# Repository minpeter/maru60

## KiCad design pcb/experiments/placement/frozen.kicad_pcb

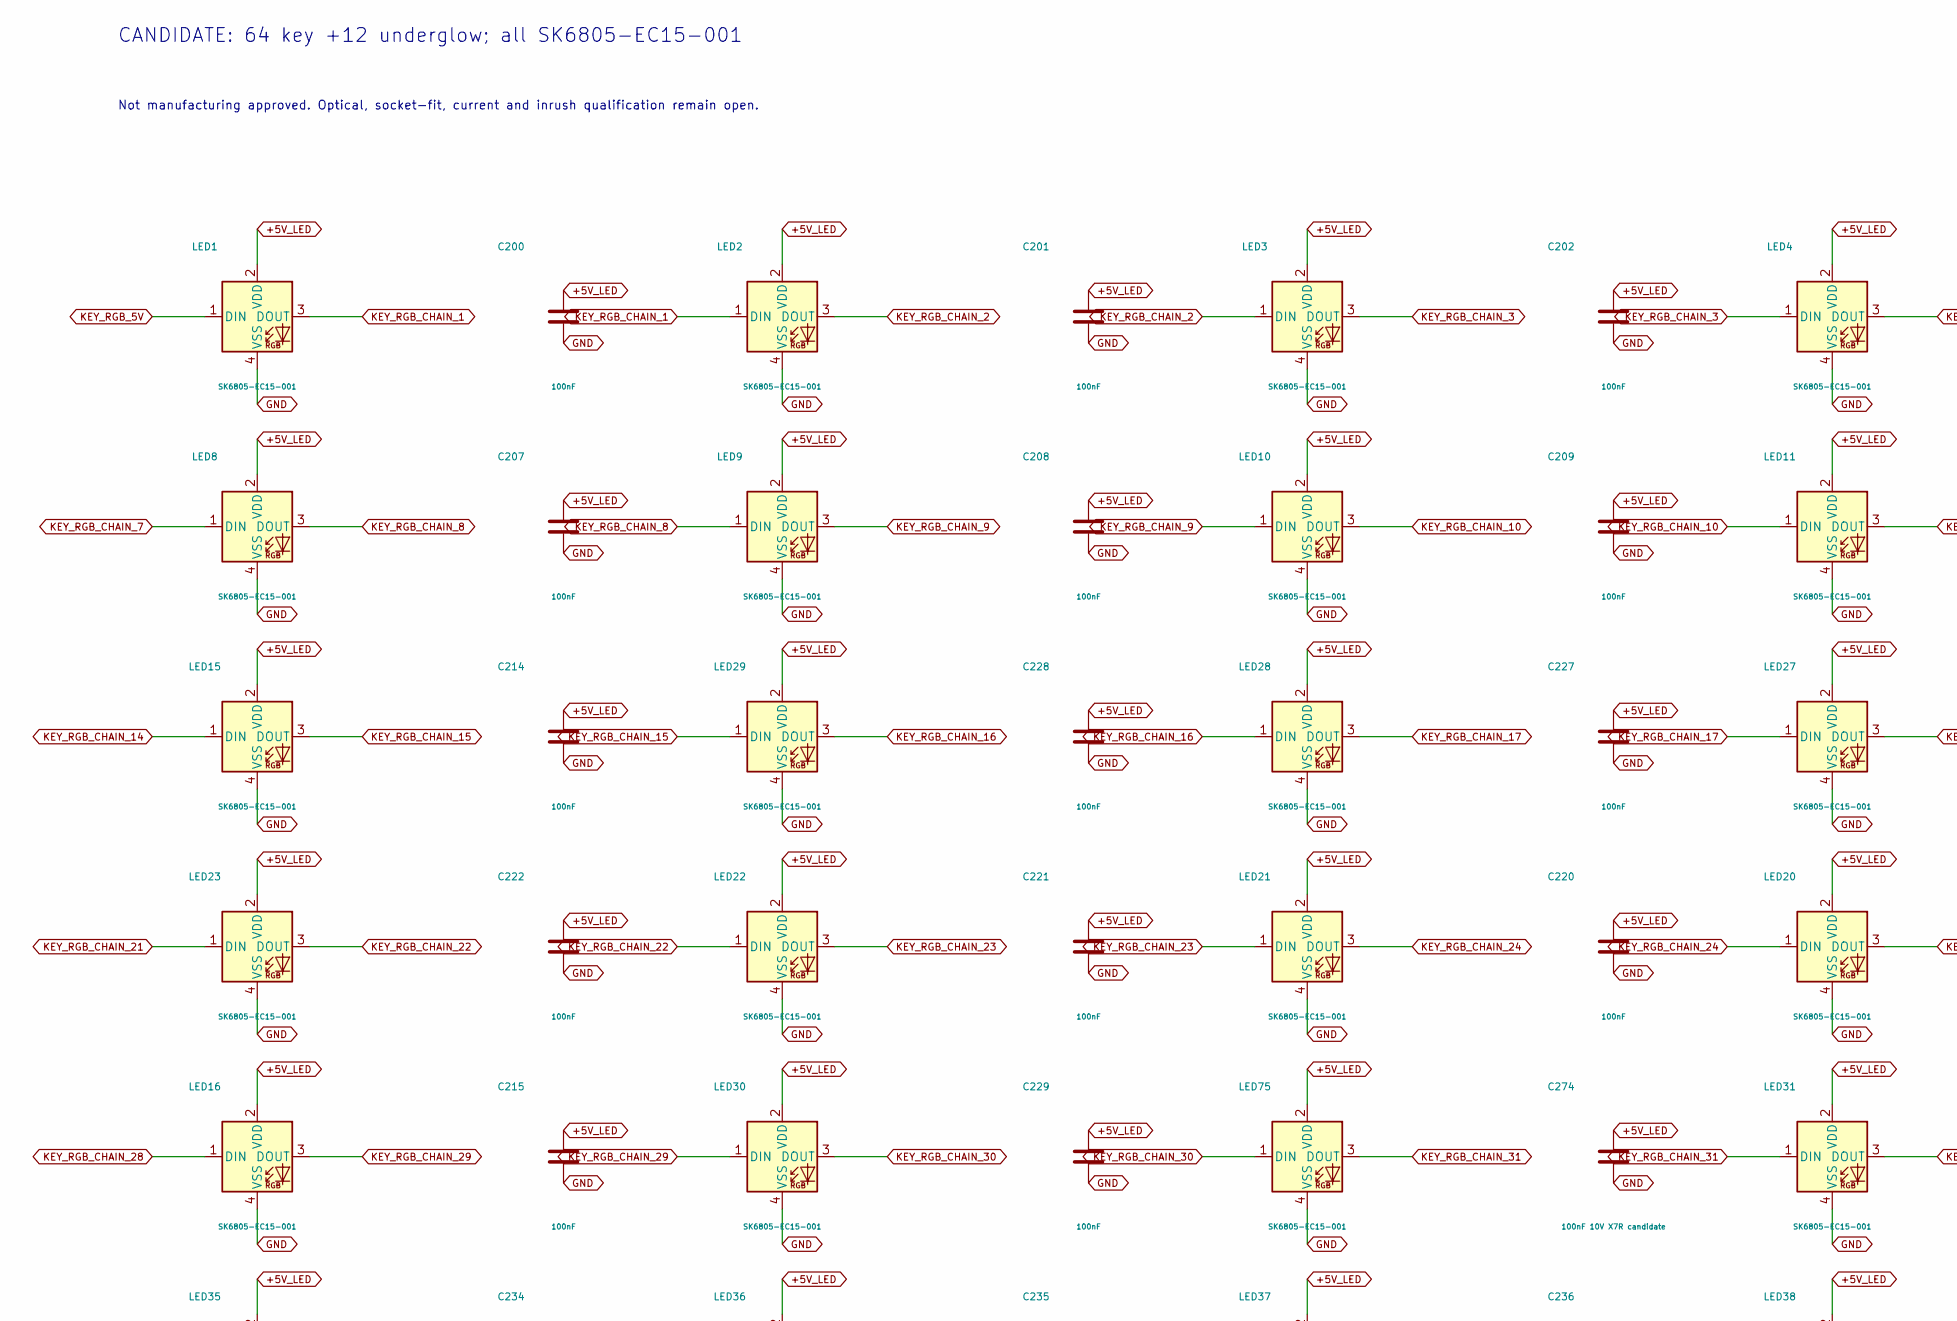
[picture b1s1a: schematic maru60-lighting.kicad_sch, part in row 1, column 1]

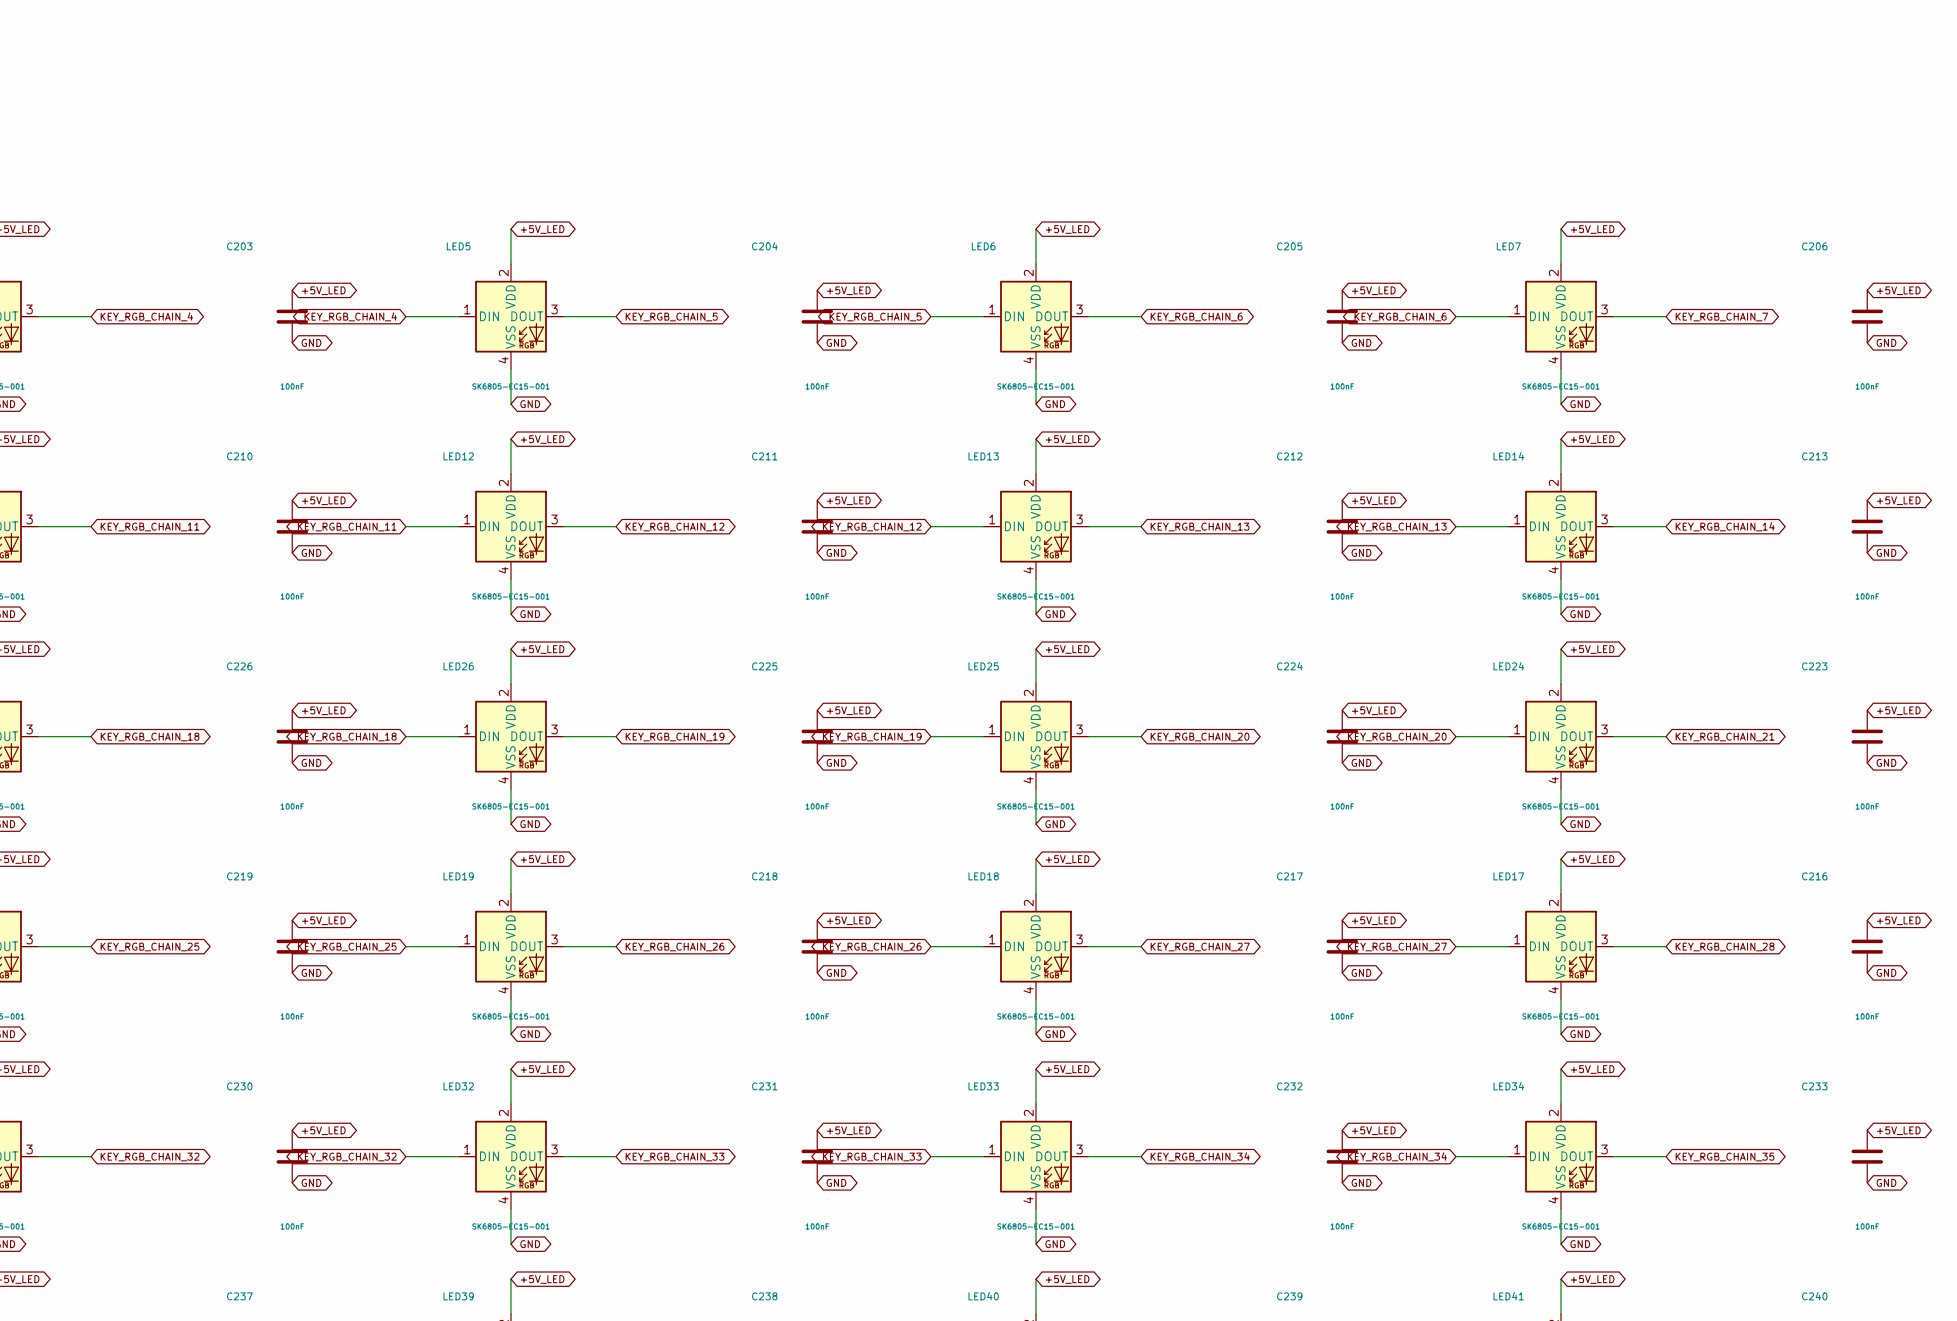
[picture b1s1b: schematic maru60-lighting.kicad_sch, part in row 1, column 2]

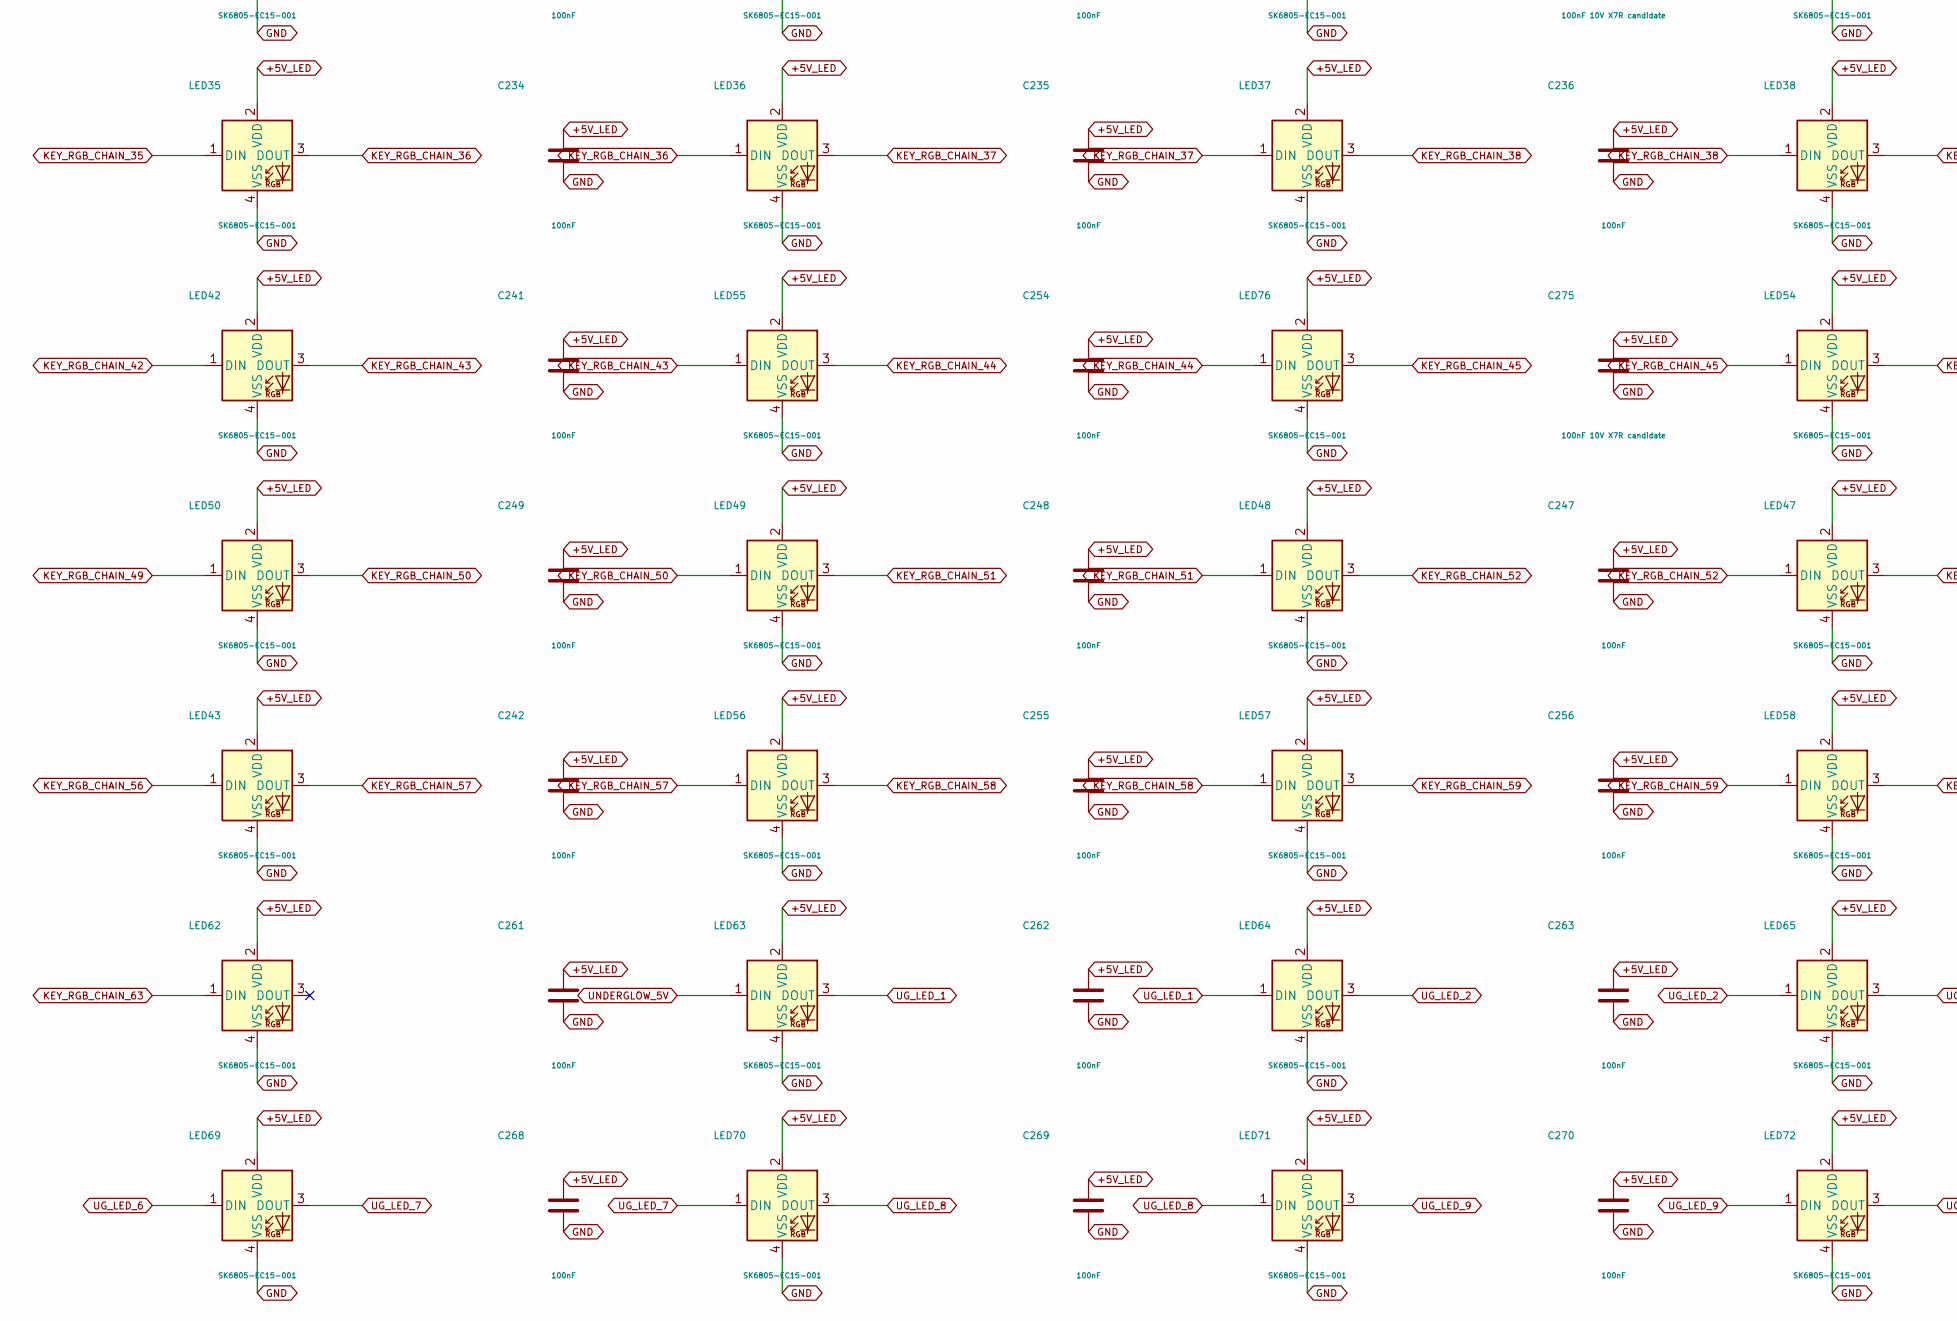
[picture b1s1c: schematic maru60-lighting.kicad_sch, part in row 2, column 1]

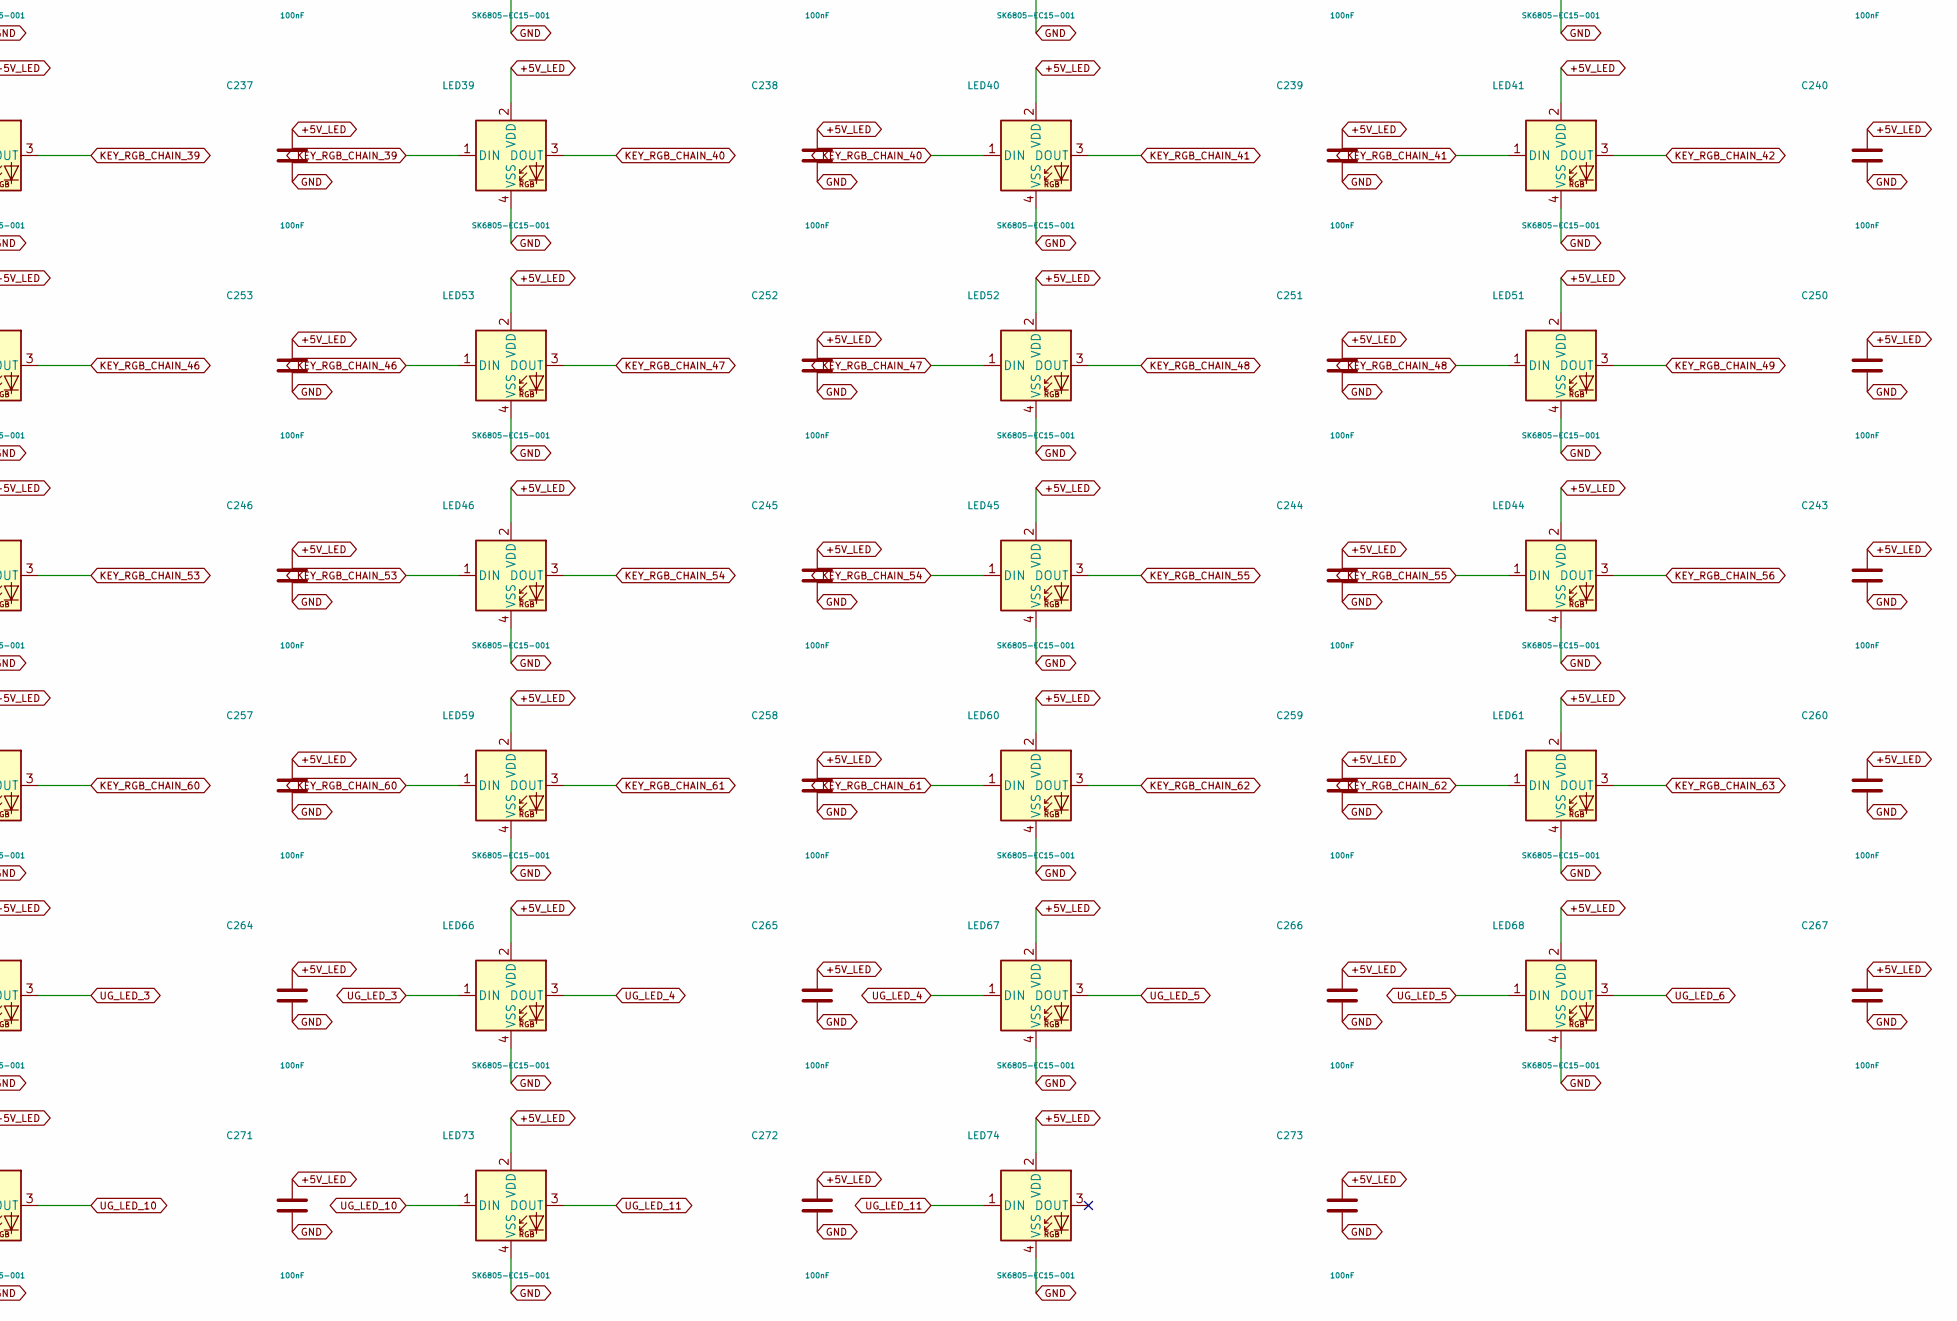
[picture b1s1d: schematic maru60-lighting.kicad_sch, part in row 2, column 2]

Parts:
C200, C201, C202, C203, C204, C205, C206, C207, C208, C209, C210, C211, C212, C213, C214, C215, C216, C217, C218, C219, C220, C221, C222, C223, C224, C225, C226, C227, C228, C229, C230, C231, C232, C233, C234, C235, C236, C237, C238, C239, C240, C241, C242, C243, C244, C245, C246, C247, C248, C249, C250, C251, C252, C253, C254, C255, C256, C257, C258, C259, C260, C261, C262, C263, C264, C265, C266, C267, C268, C269, C270, C271, C272, C273: 100nF; C_0402_1005Metric
C274, C275: 100nF 10V X7R candidate; C_0402_1005Metric
LED1, LED2, LED3, LED4, LED5, LED6, LED7, LED8, LED9, LED10, LED11, LED12, LED13, LED14, LED15, LED16, LED17, LED18, LED19, LED20, LED21, LED22, LED23, LED24, LED25, LED26, LED27, LED28, LED29, LED30, LED31, LED32, LED33, LED34, LED35, LED36, LED37, LED38, LED39, LED40, LED41, LED42, LED43, LED44, LED45, LED46, LED47, LED48, LED49, LED50, LED51, LED52, LED53, LED54, LED55, LED56, LED57, LED58, LED59, LED60, LED61, LED62, LED63, LED64, LED65, LED66, LED67, LED68, LED69, LED70, LED71, LED72, LED73, LED74, LED75, LED76: SK6805-EC15-001; LED_SK6805_EC15_001_Recommended_Candidate

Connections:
+5V_LED: C200.1, C201.1, C202.1, C203.1, C204.1, C205.1, C206.1, C207.1, C208.1, C209.1, C210.1, C211.1, C212.1, C213.1, C214.1, C215.1, C216.1, C217.1, C218.1, C219.1, C220.1, C221.1, C222.1, C223.1, C224.1, C225.1, C226.1, C227.1, C228.1, C229.1, C230.1, C231.1, C232.1, C233.1, C234.1, C235.1, C236.1, C237.1, C238.1, C239.1, C240.1, C241.1, C242.1, C243.1, C244.1, C245.1, C246.1, C247.1, C248.1, C249.1, C250.1, C251.1, C252.1, C253.1, C254.1, C255.1, C256.1, C257.1, C258.1, C259.1, C260.1, C261.1, C262.1, C263.1, C264.1, C265.1, C266.1, C267.1, C268.1, C269.1, C270.1, C271.1, C272.1, C273.1, C274.1, C275.1, LED1.2 (VDD), LED2.2 (VDD), LED3.2 (VDD), LED4.2 (VDD), LED5.2 (VDD), LED6.2 (VDD), LED7.2 (VDD), LED8.2 (VDD), LED9.2 (VDD), LED10.2 (VDD), LED11.2 (VDD), LED12.2 (VDD), LED13.2 (VDD), LED14.2 (VDD), LED15.2 (VDD), LED16.2 (VDD), LED17.2 (VDD), LED18.2 (VDD), LED19.2 (VDD), LED20.2 (VDD), LED21.2 (VDD), LED22.2 (VDD), LED23.2 (VDD), LED24.2 (VDD), LED25.2 (VDD), LED26.2 (VDD), LED27.2 (VDD), LED28.2 (VDD), LED29.2 (VDD), LED30.2 (VDD), LED31.2 (VDD), LED32.2 (VDD), LED33.2 (VDD), LED34.2 (VDD), LED35.2 (VDD), LED36.2 (VDD), LED37.2 (VDD), LED38.2 (VDD), LED39.2 (VDD), LED40.2 (VDD), LED41.2 (VDD), LED42.2 (VDD), LED43.2 (VDD), LED44.2 (VDD), LED45.2 (VDD), LED46.2 (VDD), LED47.2 (VDD), LED48.2 (VDD), LED49.2 (VDD), LED50.2 (VDD), LED51.2 (VDD), LED52.2 (VDD), LED53.2 (VDD), LED54.2 (VDD), LED55.2 (VDD), LED56.2 (VDD), LED57.2 (VDD), LED58.2 (VDD), LED59.2 (VDD), LED60.2 (VDD), LED61.2 (VDD), LED62.2 (VDD), LED63.2 (VDD), LED64.2 (VDD), LED65.2 (VDD), LED66.2 (VDD), LED67.2 (VDD), LED68.2 (VDD), LED69.2 (VDD), LED70.2 (VDD), LED71.2 (VDD), LED72.2 (VDD), LED73.2 (VDD), LED74.2 (VDD), LED75.2 (VDD), LED76.2 (VDD); also elsewhere on the board
GND: C200.2, C201.2, C202.2, C203.2, C204.2, C205.2, C206.2, C207.2, C208.2, C209.2, C210.2, C211.2, C212.2, C213.2, C214.2, C215.2, C216.2, C217.2, C218.2, C219.2, C220.2, C221.2, C222.2, C223.2, C224.2, C225.2, C226.2, C227.2, C228.2, C229.2, C230.2, C231.2, C232.2, C233.2, C234.2, C235.2, C236.2, C237.2, C238.2, C239.2, C240.2, C241.2, C242.2, C243.2, C244.2, C245.2, C246.2, C247.2, C248.2, C249.2, C250.2, C251.2, C252.2, C253.2, C254.2, C255.2, C256.2, C257.2, C258.2, C259.2, C260.2, C261.2, C262.2, C263.2, C264.2, C265.2, C266.2, C267.2, C268.2, C269.2, C270.2, C271.2, C272.2, C273.2, C274.2, C275.2, LED1.4 (VSS), LED2.4 (VSS), LED3.4 (VSS), LED4.4 (VSS), LED5.4 (VSS), LED6.4 (VSS), LED7.4 (VSS), LED8.4 (VSS), LED9.4 (VSS), LED10.4 (VSS), LED11.4 (VSS), LED12.4 (VSS), LED13.4 (VSS), LED14.4 (VSS), LED15.4 (VSS), LED16.4 (VSS), LED17.4 (VSS), LED18.4 (VSS), LED19.4 (VSS), LED20.4 (VSS), LED21.4 (VSS), LED22.4 (VSS), LED23.4 (VSS), LED24.4 (VSS), LED25.4 (VSS), LED26.4 (VSS), LED27.4 (VSS), LED28.4 (VSS), LED29.4 (VSS), LED30.4 (VSS), LED31.4 (VSS), LED32.4 (VSS), LED33.4 (VSS), LED34.4 (VSS), LED35.4 (VSS), LED36.4 (VSS), LED37.4 (VSS), LED38.4 (VSS), LED39.4 (VSS), LED40.4 (VSS), LED41.4 (VSS), LED42.4 (VSS), LED43.4 (VSS), LED44.4 (VSS), LED45.4 (VSS), LED46.4 (VSS), LED47.4 (VSS), LED48.4 (VSS), LED49.4 (VSS), LED50.4 (VSS), LED51.4 (VSS), LED52.4 (VSS), LED53.4 (VSS), LED54.4 (VSS), LED55.4 (VSS), LED56.4 (VSS), LED57.4 (VSS), LED58.4 (VSS), LED59.4 (VSS), LED60.4 (VSS), LED61.4 (VSS), LED62.4 (VSS), LED63.4 (VSS), LED64.4 (VSS), LED65.4 (VSS), LED66.4 (VSS), LED67.4 (VSS), LED68.4 (VSS), LED69.4 (VSS), LED70.4 (VSS), LED71.4 (VSS), LED72.4 (VSS), LED73.4 (VSS), LED74.4 (VSS), LED75.4 (VSS), LED76.4 (VSS); also elsewhere on the board
KEY_RGB_5V: LED1.1 (DIN); also elsewhere on the board
KEY_RGB_CHAIN_1: LED1.3 (DOUT), LED2.1 (DIN)
KEY_RGB_CHAIN_2: LED2.3 (DOUT), LED3.1 (DIN)
KEY_RGB_CHAIN_3: LED3.3 (DOUT), LED4.1 (DIN)
KEY_RGB_CHAIN_4: LED4.3 (DOUT), LED5.1 (DIN)
KEY_RGB_CHAIN_5: LED5.3 (DOUT), LED6.1 (DIN)
KEY_RGB_CHAIN_6: LED6.3 (DOUT), LED7.1 (DIN)
KEY_RGB_CHAIN_7: LED7.3 (DOUT), LED8.1 (DIN)
KEY_RGB_CHAIN_8: LED8.3 (DOUT), LED9.1 (DIN)
KEY_RGB_CHAIN_9: LED9.3 (DOUT), LED10.1 (DIN)
KEY_RGB_CHAIN_10: LED10.3 (DOUT), LED11.1 (DIN)
KEY_RGB_CHAIN_11: LED11.3 (DOUT), LED12.1 (DIN)
KEY_RGB_CHAIN_12: LED12.3 (DOUT), LED13.1 (DIN)
KEY_RGB_CHAIN_13: LED13.3 (DOUT), LED14.1 (DIN)
KEY_RGB_CHAIN_14: LED14.3 (DOUT), LED15.1 (DIN)
KEY_RGB_CHAIN_15: LED15.3 (DOUT), LED29.1 (DIN)
KEY_RGB_CHAIN_16: LED28.1 (DIN), LED29.3 (DOUT)
KEY_RGB_CHAIN_17: LED27.1 (DIN), LED28.3 (DOUT)
KEY_RGB_CHAIN_18: LED26.1 (DIN), LED27.3 (DOUT)
KEY_RGB_CHAIN_19: LED25.1 (DIN), LED26.3 (DOUT)
KEY_RGB_CHAIN_20: LED24.1 (DIN), LED25.3 (DOUT)
KEY_RGB_CHAIN_21: LED23.1 (DIN), LED24.3 (DOUT)
KEY_RGB_CHAIN_22: LED22.1 (DIN), LED23.3 (DOUT)
KEY_RGB_CHAIN_23: LED21.1 (DIN), LED22.3 (DOUT)
KEY_RGB_CHAIN_24: LED20.1 (DIN), LED21.3 (DOUT)
KEY_RGB_CHAIN_25: LED19.1 (DIN), LED20.3 (DOUT)
KEY_RGB_CHAIN_26: LED18.1 (DIN), LED19.3 (DOUT)
KEY_RGB_CHAIN_27: LED17.1 (DIN), LED18.3 (DOUT)
KEY_RGB_CHAIN_28: LED16.1 (DIN), LED17.3 (DOUT)
KEY_RGB_CHAIN_29: LED16.3 (DOUT), LED30.1 (DIN)
KEY_RGB_CHAIN_30: LED30.3 (DOUT), LED75.1 (DIN)
KEY_RGB_CHAIN_31: LED31.1 (DIN), LED75.3 (DOUT)
KEY_RGB_CHAIN_32: LED31.3 (DOUT), LED32.1 (DIN)
KEY_RGB_CHAIN_33: LED32.3 (DOUT), LED33.1 (DIN)
KEY_RGB_CHAIN_34: LED33.3 (DOUT), LED34.1 (DIN)
KEY_RGB_CHAIN_35: LED34.3 (DOUT), LED35.1 (DIN)
KEY_RGB_CHAIN_36: LED35.3 (DOUT), LED36.1 (DIN)
KEY_RGB_CHAIN_37: LED36.3 (DOUT), LED37.1 (DIN)
KEY_RGB_CHAIN_38: LED37.3 (DOUT), LED38.1 (DIN)
KEY_RGB_CHAIN_39: LED38.3 (DOUT), LED39.1 (DIN)
KEY_RGB_CHAIN_40: LED39.3 (DOUT), LED40.1 (DIN)
KEY_RGB_CHAIN_41: LED40.3 (DOUT), LED41.1 (DIN)
KEY_RGB_CHAIN_42: LED41.3 (DOUT), LED42.1 (DIN)
KEY_RGB_CHAIN_43: LED42.3 (DOUT), LED55.1 (DIN)
KEY_RGB_CHAIN_44: LED55.3 (DOUT), LED76.1 (DIN)
KEY_RGB_CHAIN_45: LED54.1 (DIN), LED76.3 (DOUT)
KEY_RGB_CHAIN_46: LED53.1 (DIN), LED54.3 (DOUT)
KEY_RGB_CHAIN_47: LED52.1 (DIN), LED53.3 (DOUT)
KEY_RGB_CHAIN_48: LED51.1 (DIN), LED52.3 (DOUT)
KEY_RGB_CHAIN_49: LED50.1 (DIN), LED51.3 (DOUT)
KEY_RGB_CHAIN_50: LED49.1 (DIN), LED50.3 (DOUT)
KEY_RGB_CHAIN_51: LED48.1 (DIN), LED49.3 (DOUT)
KEY_RGB_CHAIN_52: LED47.1 (DIN), LED48.3 (DOUT)
KEY_RGB_CHAIN_53: LED46.1 (DIN), LED47.3 (DOUT)
KEY_RGB_CHAIN_54: LED45.1 (DIN), LED46.3 (DOUT)
KEY_RGB_CHAIN_55: LED44.1 (DIN), LED45.3 (DOUT)
KEY_RGB_CHAIN_56: LED43.1 (DIN), LED44.3 (DOUT)
KEY_RGB_CHAIN_57: LED43.3 (DOUT), LED56.1 (DIN)
KEY_RGB_CHAIN_58: LED56.3 (DOUT), LED57.1 (DIN)
KEY_RGB_CHAIN_59: LED57.3 (DOUT), LED58.1 (DIN)
KEY_RGB_CHAIN_60: LED58.3 (DOUT), LED59.1 (DIN)
KEY_RGB_CHAIN_61: LED59.3 (DOUT), LED60.1 (DIN)
KEY_RGB_CHAIN_62: LED60.3 (DOUT), LED61.1 (DIN)
KEY_RGB_CHAIN_63: LED61.3 (DOUT), LED62.1 (DIN)
KEY_RGB_CHAIN_64: LED62.3 (DOUT)
UG_LED_1: LED63.3 (DOUT), LED64.1 (DIN)
UG_LED_2: LED64.3 (DOUT), LED65.1 (DIN)
UG_LED_3: LED65.3 (DOUT), LED66.1 (DIN)
UG_LED_4: LED66.3 (DOUT), LED67.1 (DIN)
UG_LED_5: LED67.3 (DOUT), LED68.1 (DIN)
UG_LED_6: LED68.3 (DOUT), LED69.1 (DIN)
UG_LED_7: LED69.3 (DOUT), LED70.1 (DIN)
UG_LED_8: LED70.3 (DOUT), LED71.1 (DIN)
UG_LED_9: LED71.3 (DOUT), LED72.1 (DIN)
UG_LED_10: LED72.3 (DOUT), LED73.1 (DIN)
UG_LED_11: LED73.3 (DOUT), LED74.1 (DIN)
UG_LED_12: LED74.3 (DOUT)
UNDERGLOW_5V: LED63.1 (DIN); also elsewhere on the board

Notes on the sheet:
CANDIDATE: 64 key +12 underglow; all SK6805-EC15-001
Not manufacturing approved. Optical, socket-fit, current and inrush qualification remain open.
